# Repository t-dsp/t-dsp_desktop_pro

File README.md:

# T-DSP Desktop Pro

**Part of the [T-DSP](https://t-dsp.com) open modular audio platform.**

A desktop audio backplane (120mm x 100mm) that serves as the central hub for the T-DSP modular audio ecosystem. Hosts a Teensy 4.1, ESP32, and T-DSP TAC5212 pro audio codec module on an 8-layer PCB designed for studio-quality signal integrity.

| | |
|:---:|:---:|
|  |  |
|  |  |

**[View 3D Render Gallery](https://t-dsp.github.io/t-dsp_desktop_pro/gallery.html)** -- interactive slideshow of all board views

## About T-DSP

T-DSP is an open modular audio platform designed for musicians, engineers, and developers who want powerful digital signal processing in a flexible, hackable format. Built around the [Teensy](https://www.pjrc.com/teensy/) microcontroller and the [Teensy Audio Library](https://www.pjrc.com/teensy/td_libs_Audio.html), T-DSP combines studio-quality audio with a growing library of open-source modules for mixing, synthesis, effects, and more.

Whether you're building a custom digital mixer, crafting a unique instrument, or prototyping audio products, T-DSP gives you the tools to bring your ideas to life.

Join the community, contribute to the library, or grab a module and start patching. Learn more at [t-dsp.com](https://t-dsp.com).

## Overview

The Desktop Pro is a **backplane PCB** that hosts a Teensy 4.1, ESP32, and T-DSP codec module alongside supporting ICs to create a complete audio development platform. It provides all the connectors, processing, networking, and user interface needed to build desktop audio devices.

## Processing

- **Teensy 4.1** -- ARM Cortex-M7 running the Teensy Audio Library for real-time audio processing (mixing, effects, synthesis, routing). Also receives USB Audio.
- **ESP32** -- UI controller, WiFi/Bluetooth connectivity. Runs the display, buttons, and encoder, and sends commands to the Teensy over serial.
- **T-DSP TAC5212 Module** -- Professional stereo audio codec (ADC + DAC) with mic preamp, line, and instrument inputs

## On-Board ICs

| Ref | Part | Function |
|-----|------|----------|
| U1 | Teensy 4.1 | Audio DSP (ARM Cortex-M7) |
| U2 | ESP32-DevKitC | UI controller, WiFi/Bluetooth |
| U3 | TPS2116DRL | Power multiplexer (dual input selection) |
| U4 | H11L1SM | Optoisolator (MIDI input) |
| U5-U8 | SN74LVC2G125DCTR | Dual bus buffers (4x) |
| U9 | 74HCT2G17GW | Dual Schmitt trigger buffer |
| U10 | TPD4E02B04DQA | USB ESD protection (4-channel) |
| IC1 | 74HCT2G125DC | Logic level shifter |
| D5 | TPD1E10B06DPYT | VBUS ESD protection |
| Q1, Q2 | DMG2307L-7 | P-FET reverse polarity protection |

## Connectivity

### Audio I/O
- **RCA outputs** -- Stereo analog audio output
- **RCA inputs** -- Stereo analog audio input
- **Headphone output** -- 1/4" (6.35mm) or 3.5mm headphone jack
- **S/PDIF** -- Digital audio input and output

### USB
- **USB-C DEVICE** -- Power and USB Audio to Teensy with ESD protection (TPD4E02B04 + TPD1E10B06)
- **USB-A HOST** -- USB host connector

### MIDI
- **MIDI input** -- 3.5mm TRS with optical isolation (H11L1)
- **MIDI GPIO** -- Configurable for MIDI in, out, or thru

### Power
- **Dual power input** -- USB-C or external supply via JST-XH header, with TPS2116 power multiplexer for automatic switchover
- **Reverse polarity protection** -- P-channel MOSFET (DMG2307L-7) on both 5V and 12V inputs
- **Power indicators** -- LED indicators for 5V and 12V rails

### Storage
- **SD card** -- Accessible via Teensy 4.1 built-in SD slot

## Expansion

- **2x TDM expansion headers** (2x10 pin, 2.54mm) -- Connect T-DSP audio modules
  - TDM digital audio bus (BCLK, LRCK, DATA_IN, DATA_OUT, MCLK)
  - I2C control bus (SDA, SCL)
  - Power rails (3.3V, 5V, 12V, GND)
  - Control pins (Held-high, Held-low)
- Modules can be soldered directly or socketed with pin headers
- Multiple modules can be chained on the same TDM bus

## User Interface

The backplane exposes interface-ready GPIO headers for flexible UI connectivity, supporting popular interface options compatible with the ESP32.

- **GPIO header** -- Active-low buttons, rotary encoder, and display connections for tactile UI
- **OLED display header** (128x64, SSD1306) -- Status and menu-driven UI
- **3.2" TFT touchscreen header** (ILI9341) -- Touchscreen UI
- **SK6812 addressable LED header** -- ESP32 and Teensy status indication, plus LED strip control

## Board Design

- **8-layer PCB** with dedicated ground and power planes for low-noise analog performance
- **120mm x 100mm** board dimensions
- LDO voltage regulation for clean analog power
- Buffered digital outputs for reliable module distribution
- Separate analog and digital ground domains

## Project Files

| Directory | Contents |
|-----------|----------|
| `/3d_models/` | 3D models for PCB components |
| `/documentation/` | [Schematic PDF](documentation/t-dsp-desktop-pro-schematic.pdf), board images, and reference docs |
| `/lib_fp/` | Custom KiCad footprint libraries |
| `/lib_sch/` | Custom KiCad schematic symbol libraries |
| `/manufacturing/` | CI-generated manufacturing outputs (gerbers, BOM, pick & place, PDFs) |
| `/panel/` | Panelized board layouts for production |
| `/pages/` | [3D Render Gallery](https://t-dsp.github.io/t-dsp_desktop_pro/gallery.html), [Interactive BOM](https://t-dsp.github.io/t-dsp_desktop_pro/ibom.html) |

View the design files directly in your browser with KiCanvas: [Schematic](https://kicanvas.org/?github=https://github.com/t-dsp/t-dsp_desktop_pro/blob/main/t-dsp_desktop_pro.kicad_sch) | [PCB](https://kicanvas.org/?github=https://github.com/t-dsp/t-dsp_desktop_pro/blob/main/t-dsp_desktop_pro.kicad_pcb)

## Status

This board is under active development. The current revision includes USB-C ESD protection, reverse polarity protection, and boot pin corrections from the pre-production review.

If you build one, we'd love to hear how it goes -- please open an issue or reach out with your findings.

## Contact

For consulting, custom backplane design, or commercial licensing inquiries, reach out via [LinkedIn](https://linkedin.com/in/jayshoe).

## License

This project is licensed under the [Creative Commons Attribution-NonCommercial-ShareAlike 4.0 International (CC BY-NC-SA 4.0)](https://creativecommons.org/licenses/by-nc-sa/4.0/).

You are free to share and adapt this work for non-commercial purposes, as long as you give appropriate credit and distribute any derivatives under the same license.

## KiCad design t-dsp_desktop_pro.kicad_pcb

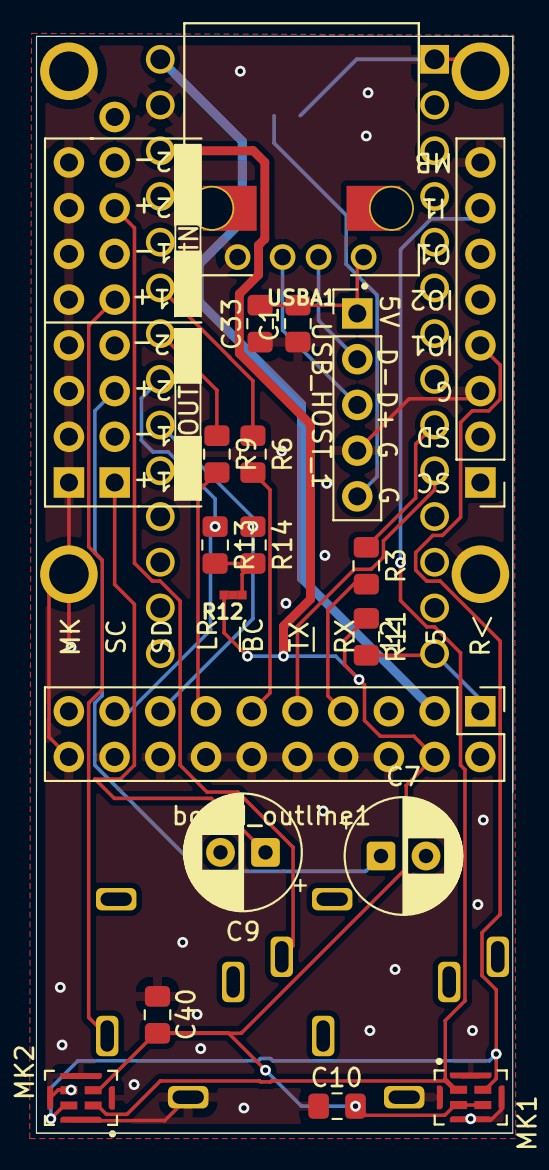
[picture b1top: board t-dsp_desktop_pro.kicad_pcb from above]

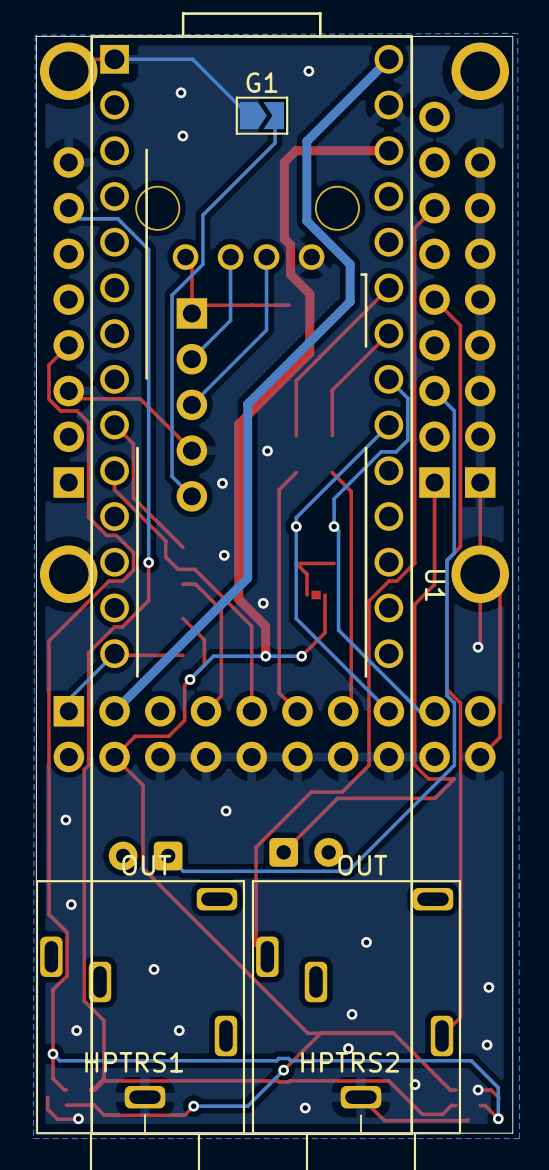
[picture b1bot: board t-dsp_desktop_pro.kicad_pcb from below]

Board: 2 copper layers, 26.5 x 60.9 mm, 22 parts (4 on the bottom side), 24 nets.

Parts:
C1: 1 uF; C_0805_2012Metric_Pad1.15x1.40mm_HandSolder
C7, C9: 470 uF Electrolytic Audio-Grade; CP_Radial_D6.3mm_P2.50mm
C10, C40: 0.1uF; C_0805_2012Metric_Pad1.15x1.40mm_HandSolder
C33: 10 uF; C_0805_2012Metric_Pad1.15x1.40mm_HandSolder
G1: jumper; SolderJumper-2_P1.3mm_Open_TrianglePad1.0x1.5mm
HPTRS1, HPTRS2: 3.5mm TRS - 35RAPC3BH3; 35RAPC3BH3
MK1, MK2: SPK0641HT4H-1
R3, R6, R9: 49.9 ohm; R_0805_2012Metric_Pad1.15x1.40mm_HandSolder
R11: 10k; R_0805_2012Metric_Pad1.15x1.40mm_HandSolder
R12: 0 ohm; jumper_slice
R13, R14: 2.21k ohm; R_0805_2012Metric_Pad1.15x1.40mm_HandSolder
U1: Teensy 4.1 - DEVKIT; Teensy41_simple
USBA1: USB A Host - TE 292303-5; TE_292303-5_USB_A_tight_fit
USB_HOST_1: header; USB_IN1
board_outline1: TAC5212 Module; audio_module_board_outline_50x34.5_d1_ADAPTOR

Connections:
3.3V: C10.1, C40.1, MK1.3 (SELECT), MK1.4 (VDD), MK2.4 (VDD), R11.1, R12.2, U1.46 (3V3), board_outline1.4 (3.3V)
5V: U1.48 (VIN), board_outline1.3 (5V)
7_OUT1A: R3.2, board_outline1.7 (DSP_DOUT)
8_IN1: U1.10 (8_TX2_IN1), board_outline1.9 (DSP_DIN)
35_TX8_RESET: R11.2, U1.14 (12_MISO_MQSL), board_outline1.1 (HELD_HIGH)
/AUDIO_IN1P: HPTRS2.5, board_outline1.29 (IN1P)
/AUDIO_IN2P: HPTRS2.2, board_outline1.33 (IN2P)
/AUDIO_OUT2P: C7.1, board_outline1.25 (OUT2P)
/AUDIO_OUTP: C9.1, board_outline1.21 (OUTP)
BCLK1: R6.2, board_outline1.11 (BCLK)
GND: C1.2, C10.2, C33.2, C40.2, G1.1, HPTRS1.1, HPTRS2.1, MK1.5 (GND), MK1.6 (GND), MK1.7 (GND), MK1.8 (GND), MK2.3 (SELECT), MK2.5 (GND), MK2.6 (GND), MK2.7 (GND), MK2.8 (GND), U1.1 (GND), U1.47 (GND), USBA1.4 (GND), USB_HOST_1.4 (GND), board_outline1.6 (GNDD), board_outline1.8 (GNDD), board_outline1.10 (GNDD), board_outline1.12 (GNDD), board_outline1.14 (GNDD), board_outline1.16 (GNDD), board_outline1.18 (GNDD), board_outline1.20 (GNDD), board_outline1.22 (AGND), board_outline1.24 (AGND), board_outline1.26 (AGND), board_outline1.28 (AGND), board_outline1.30 (AGND), board_outline1.32 (AGND), board_outline1.34 (AGND), board_outline1.36 (AGND), board_outline1.39 (GNDD), board_outline1.44 (GNDD), board_outline1.49 (AGND), board_outline1.50 (AGND), board_outline1.51 (DGND), board_outline1.52 (DGND)
GPIGPI1: MK1.1 (DATA), MK2.1 (DATA), board_outline1.43 (GPI1)
GPIO1: MK1.2 (CLOCK), MK2.2 (CLOCK), board_outline1.40 (GPIO1)
HOST_5V: C1.1, C33.1, USBA1.1 (VBUS), USB_HOST_1.1 (5V)
HOST_D1+: USBA1.3 (D+), USB_HOST_1.3 (D1+)
HOST_D1-: USBA1.2 (D-), USB_HOST_1.2 (D1-)
LRCK1: R9.2, board_outline1.13 (LRCK)
unnamed: R12.1, R13.2, R14.2
unnamed: R3.1, U1.9 (7_RX2_OUT1A)
unnamed: R9.1, U1.42 (20_A6_TX5_LRCLK1)
unnamed: R6.1, U1.43 (21_A7_RX5_BCLK1)
SCL0: R13.1, U1.41 (19_A5_SCL), board_outline1.17 (SCL)
SDA0: R14.1, U1.40 (18_A4_SDA), board_outline1.15 (SDA)
USB_SHIELD2: G1.2, USB_HOST_1.5 (SHIELD)

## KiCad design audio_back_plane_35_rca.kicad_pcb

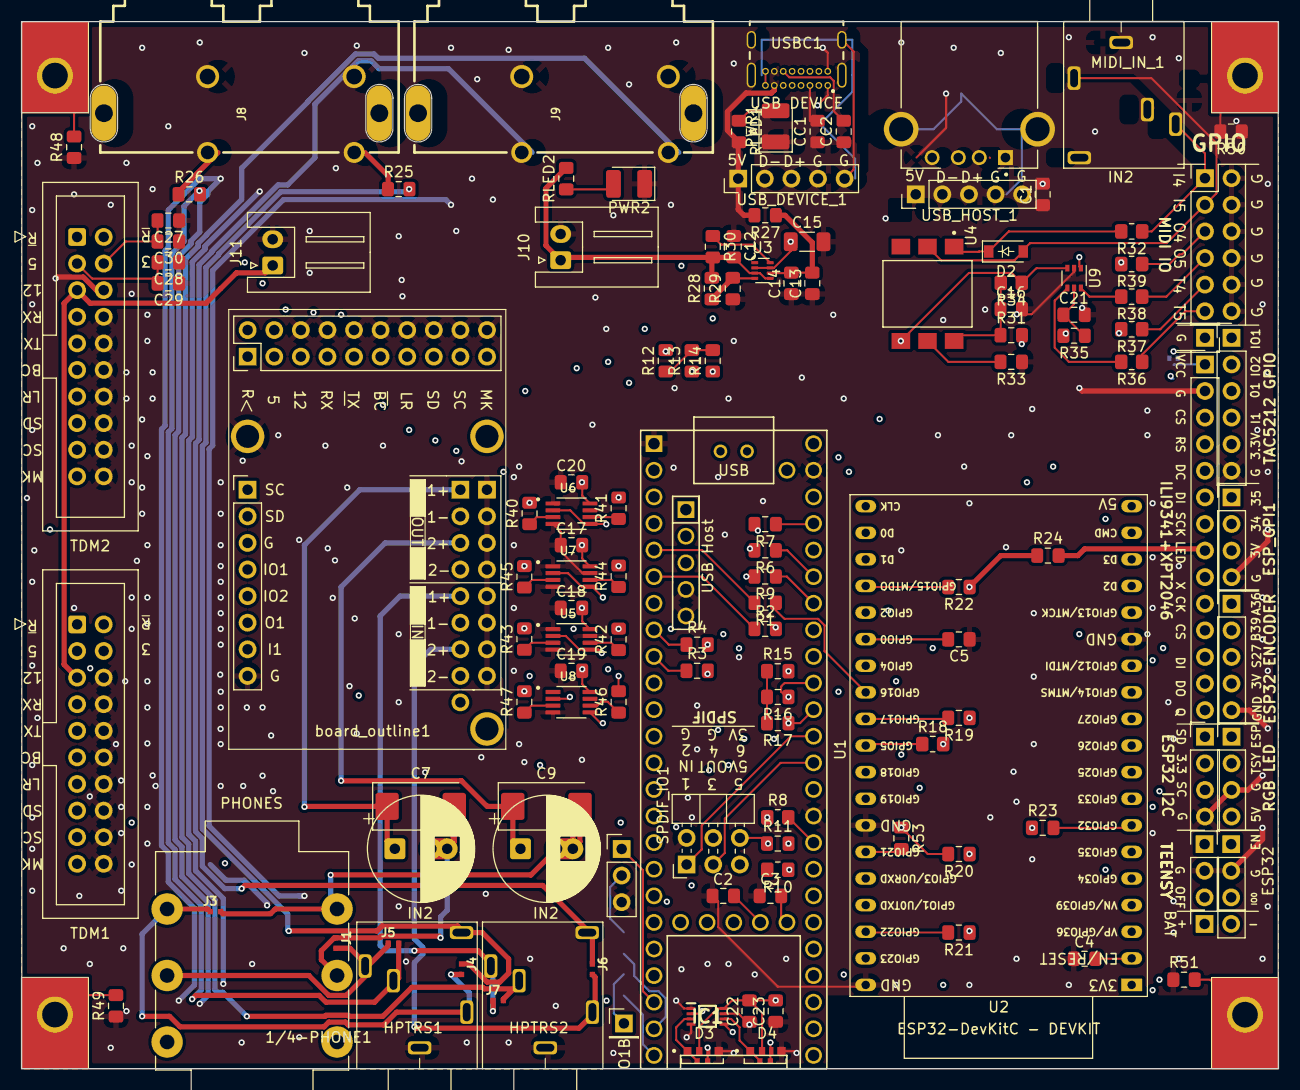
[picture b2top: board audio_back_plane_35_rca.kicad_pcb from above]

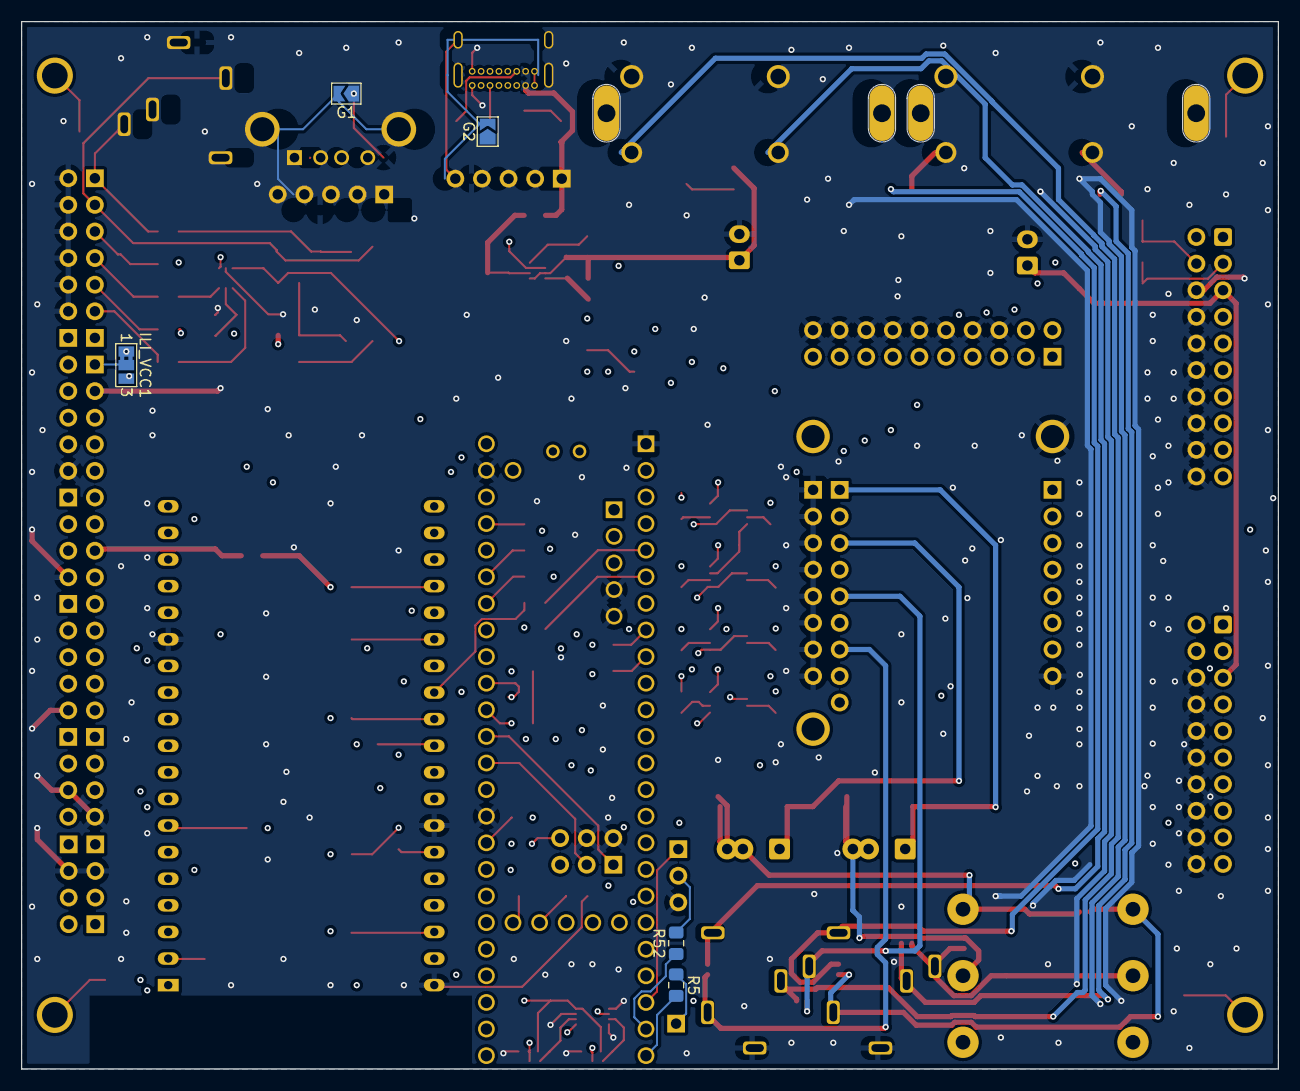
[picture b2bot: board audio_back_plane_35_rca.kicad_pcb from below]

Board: 8 copper layers, 120.0 x 100.0 mm, 138 parts (5 on the bottom side), 143 nets.

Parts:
1/4-PHONE1: NMJ6HFD2-AU; Jack_6.35mm_Neutrik_NMJ6HCD3_Horizontal
BAT1: BAT HEADER; BAT2_PinSocket_1x02_P2.54mm_Vertical
C1, C29, C30: 1 uF; C_0805_2012Metric_Pad1.15x1.40mm_HandSolder
C2, C3, C4, C5, C14, C16, C17, C18, C19, C20, C21, C22: 0.1 uF; C_0805_2012Metric_Pad1.15x1.40mm_HandSolder
C7, C9: 470 uF Electrolytic Audio-Grade; CP_Radial_D10.0mm_P5.00mm_AND_D8.0mm_P3.5mm
C12, C13, C23: 10 uF; C_0805_2012Metric_Pad1.15x1.40mm_HandSolder
C15: 100 uF; C_1206_3216Metric_Pad1.33x1.80mm_HandSolder
C27, C28: 47uF; C_0805_2012Metric_Pad1.15x1.40mm_HandSolder
CC1, CC2: 5.1k ohm; R_0805_2012Metric_Pad1.15x1.40mm_HandSolder
D1: HEADER; TAC5212 GPIO_PinHeader_1x06_P2.54mm_Vertical
D2: Diode - 1N4148; D_SOD-123
D3, D4: Side Light LED - SK6812; SK6812-32228SMD-Reverse-Mount_mod
ESP_I1: ESP32 I2C HEADER; ESP_I2C_PinHeader_1x04_P2.54mm_Vertical
ESP_PROG1: header; E_PROG1_PinHeader_1x03_P2.54mm_Vertical
ESP_R_ENC1: header; ESP_R_ENC0_PinHeader_1x05_P2.54mm_Vertical
G1, G2: jumper; SolderJumper-2_P1.3mm_Open_TrianglePad1.0x1.5mm
GPI1: ESP32 GPI HEADER; GPI1_PinHeader_1x04_P2.54mm_Vertical
HPTRS1, HPTRS2: 3.5mm TRS - 35RAPC3BH3; 35RAPC3BH3
IC1: Logic Level Shifter - 74HCT2G125DC,125; SOP50P310X100-8N
ILI1: ILI9341+XPT2046; ILI9341_PinHeader_1x14_P2.54mm_Vertical
ILI_VCC1: jumper; SolderJumper-3_P1.3mm_Bridged2Bar12_Pad1.0x1.5mm_NumberLabe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
J1, J3, J4, J5, J6, J7: jumper; jumper_slice_disconnected
J2: GROUND HEADER; GPIO_GROUND_PinHeader_1x01_P2.54mm_Vertical
J8, J9: PJRAS2X1S01X; PJRAS2X1S01X_MOD2
J10, J11: JST-XH Connector -; JST_XH_S2B-XH-A_1x02_P2.50mm_Horizontal
J12: RGB LED HEADEER; LED_GPIO_PinHeader_1x04_P2.54mm_Vertical
J14: Conn_01x03; Teensy_UART3_PinHeader_1x03_P2.54mm_Vertical
J15: Conn_01x01; OUT1B_PinHeader_1x01_P2.54mm_Vertical
MIDI_IN_1: 3.5mm TRS - 35RAPC3BH3; 35RAPC3BH3
MIDI_IO1: header; MIDI_IO1
PWR1, PWR2: LED Power Indicator - 1206 5v 2.0 V Forward; D_1210_3225Metric_Pad1.42x2.65mm_HandSolder
R1, R2, R3, R4, R5, R6, R7, R9, R25, R26, R40, R41, R42, R43, R44, R45, R46, R47, R52, R53: 49.9 ohm; R_0805_2012Metric_Pad1.15x1.40mm_HandSolder
R8, R18, R32, R34, R36, R37, R38, R39: 220 ohm; R_0805_2012Metric_Pad1.20x1.40mm_HandSolder
R10: 49.9 ohm; R_0805_2012Metric_Pad1.20x1.40mm_HandSolder
R11, R13, R14, R16, R17, R19, R20, R21, R22, R23: 2.21k ohm; R_0805_2012Metric_Pad1.15x1.40mm_HandSolder
R12, R15, R24, R27, R31, R35, R48, R49, R50, R51: 0 ohm; R_0805_2012Metric_Pad1.15x1.40mm_HandSolder
R28: 16.9k ohm; R_0805_2012Metric_Pad1.15x1.40mm_HandSolder
R29, R30: 5.1k ohm; R_0805_2012Metric_Pad1.15x1.40mm_HandSolder
R33: 1.5k ohm; R_0805_2012Metric_Pad1.15x1.40mm_HandSolder
RLED1, RLED2: 2.21k ohm; R_0805_2012Metric_Pad1.15x1.40mm_HandSolder
SPDIF_IO1: header; SPDIF_PinHeader_2x03_P2.54mm_Horizontal
T108, T109, T110, T111: Tab
TDM1, TDM2: I2S /I2C EXPANSION HEADER; T-DSP_Expansion_Header_2x10_ALT_GND
T_PROG1: TEENSY SWITCH HEADER; T_PROG1_PinHeader_1x03_P2.54mm_Vertical
U1: Teensy 4.1 - DEVKIT; Teensy41_mod3
U2: ESP32-DevKitC - DEVKIT; ESP32-DevKitC_NO_COURTYARD
U3: Power Mux & Protect - TPS2116DRL; SOT-583-8
U4: Optoisolators - H11L1SM - 6-SMD, Gull Wing; IC_H11L1SM
U5, U6, U7, U8: Dual Buffer - SN74LVC2G125DCTR; SOP65P400X130-8N
U9: Dual Buffer - 74HCT2G17GW,125; SOT-363_SC-70-6
USBA1: USB A Host - TE 292303-5; TE_292303-5_USB_A
USBC1: USB C Port - Through Hole USB4085-GF-A; GCT_USB4085-GF-A_REVA4
USB_DEVICE_1: header; USB_IN1
USB_HOST_1: header; USB_IN1
board_outline1: TAC5212 Module; audio_module_board_outline_50x34.5_d1_mod
board_outline2: board_outline; audio_project_board_outline_100x120

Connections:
2_OUT2: U1.4 (2_OUT2), U2.8 (32K_XN/GPIO33/ADC1_CH5)
3.3V: C17.1, C18.1, C19.1, C20.1, C27.1, C30.1, D1.5, ESP_I1.2, ESP_R_ENC1.4, GPI1.3, ILI_VCC1.3 (B), R11.1, R12.2, R15.2, R19.1, R20.1, R21.1, R22.1, R23.1, R24.1, R31.2, SPDIF_IO1.6, TDM1.4 (GND), TDM2.4 (GND), U1.46 (3V3), U5.8 (VCC), U6.8 (VCC), U7.8 (VCC), U8.8 (VCC), board_outline1.4 (GNDD)
3_LRCLK2: R1.1, U2.27 (GPIO16)
4_BCLK2: R2.2, U2.10 (DAC_2/ADC2_CH9/GPIO26)
5V: C15.1, C22.1, C23.1, C28.1, C29.1, D3.2 (VDD), D4.2 (VDD), IC1.8 (VCC), ILI_VCC1.1 (A), J12.4, R35.2, R37.2, R39.2, SPDIF_IO1.5, TDM1.3 (5V), TDM2.3 (5V), U1.48 (VIN), U2.19 (5V), U3.2 (VOUT), U3.7 (VOUT), board_outline1.3 (5V)
5V_JST: C12.1, J10.1, R28.2, R30.2, RLED2.2, U3.3 (VIN1), U3.5 (MODE)
5V_USB: R27.2, RLED1.2, USBC1.A4 (VBUS), USBC1.A9 (VBUS), USBC1.B4 (VBUS), USBC1.B9 (VBUS), USB_DEVICE_1.1 (5V)
5_IN2: U1.7 (5_IN2), U2.9 (DAC_1/ADC2_CH8/GPIO25)
6_OUT1D: R4.2, U8.5 (2A)
6_OUT1D+: R47.2, TDM1.9 (DSP_DATA_OUT)
7_OUT1A: R3.2, U8.2 (1A)
7_OUT1A+: R46.2, TDM2.9 (DSP_DATA_OUT), board_outline1.7 (DSP_DOUT)
8_IN1: TDM2.7 (DSP_DATA_IN), U1.10 (8_TX2_IN1), board_outline1.9 (DSP_DIN)
9_OUT1C_INPUT: TDM1.7 (DSP_DATA_IN), U1.11 (9_OUT1C)
12V: J11.1, TDM1.5 (12V), TDM2.5 (12V)
14_SPDIF_OUT: SPDIF_IO1.3, U1.36 (14_A0_TX3_SPDIF_OUT)
15_SPDIF_IN: SPDIF_IO1.1, U1.37 (15_A1_RX3_SPDIF_IN)
32_OUT1B: J15.1, R5.1
34_RX8_RESET2: TDM1.2 (HELD_LOW), TDM2.2 (HELD_LOW), U1.26 (34_RX8), board_outline1.2 (HELD_LOW)
35_TX8_RESET: R11.2, TDM1.1 (HELD_HIGH), TDM2.1 (HELD_HIGH), U1.27 (35_TX8), board_outline1.1 (HELD_HIGH)
53_T_PROG: C2.1, T_PROG1.1, U1.53 (PROGRAM)
54_ON_OFF: C3.1, T_PROG1.3, U1.54 (ON_OFF)
/AUDIO_IN1P: HPTRS2.2, J7.2, board_outline1.29 (IN1P)
/AUDIO_IN2P: HPTRS2.5, J6.1, board_outline1.33 (IN2P)
/AUDIO_OUT2P: C9.1, board_outline1.25 (OUT2P)
/AUDIO_OUTP: C7.1, board_outline1.21 (OUTP)
/ESP32_IO1: U1.20 (28_RX7), U2.35 (U0TXD/GPIO1)
/ESP32_IO3: U1.21 (29_TX7), U2.34 (U0RXD/GPIO3)
/ESP32_IO21_SDA: R53.2, U2.33 (GPIO21)
/ESP32_IO22_SCL: ESP_I1.3, R21.2, U2.36 (GPIO22)
/OUTPUTA: ESP_R_ENC1.1, U1.32 (40_A16), U2.3 (SENSOR_VP/GPIO36/ADC1_CH0)
/OUTPUTB: ESP_R_ENC1.2, U1.31 (39_MISO1_OUT1A), U2.4 (SENSOR_VN/GPIO39/ADC1_CH3)
/SWITCH: ESP_R_ENC1.3, U1.30 (38_CS1_IN1), U2.11 (ADC2_CH7/GPIO27)
BCLK1: R6.2, U7.2 (1A), U7.5 (2A)
BCLK1+TDM1: R44.2, TDM2.11 (BCLK), board_outline1.11 (BCLK)
BCLK1+TDM2: R45.2, TDM1.11 (BCLK)
DEVICE_D1+: U1.67 (D+), USBC1.A6 (DP1), USB_DEVICE_1.3 (D1+)
DEVICE_D1-: U1.66 (D-), USBC1.A7 (DN1), USB_DEVICE_1.2 (D1-)
ESP32_EN: C4.1, ESP_PROG1.1, U1.29 (37_CS), U2.2 (EN/CHIP_PU/RESET)
ESP32_IO0: C5.1, ESP_PROG1.3, U1.28 (36_CS), U2.25 (*GPIO0/BOOT/ADC2_CH1)
ESP32_IO12_SPI_MISO: U1.14 (12_MISO_MQSL), U2.13 (*MTDI/GPIO12/ADC2_CH5)
ESP32_IO13_SPI_MOSI: U1.13 (11_MOSI_CTX1), U2.15 (MTCK/GPIO13/ADC2_CH4)
ESP32_IO14_SPI_SCK: U1.35 (13_SCK_LED), U2.12 (MTMS/GPIO14/ADC2_CH6)
ESP32_IO33_SPI_CS: R19.2, U1.12 (10_CS_MQSR), U2.28 (GPIO17)
ESP32_LED: IC1.2 (1A), R18.2
ESP32_LED+: D4.1 (DIN), IC1.6 (1Y)
ESP32_LED_OUT: D4.3 (DOUT), J12.1
GND: C1.2, C2.2, C3.2, C4.2, C5.2, C12.2, C13.2, C14.2, C15.2, C16.1, C17.2, C18.2, C19.2, C20.2, C21.1, C22.2, C23.2, C27.2, C28.2, C29.2, C30.2, CC1.1, CC2.1, D1.6, D3.4 (GND), D4.4 (GND), ESP_I1.4, ESP_PROG1.2, ESP_R_ENC1.5, G1.1, G2.1, GPI1.4, HPTRS1.1, HPTRS2.1, IC1.1 (~1OE), IC1.4 (GND), IC1.7 (~2OE), ILI1.2 (GND), J8.S1, J8.S2, J9.S1, J9.S2, J10.2, J11.2, J12.3, J14.3, MIDI_IN_1.1, MIDI_IO1.2, MIDI_IO1.4, MIDI_IO1.6, MIDI_IO1.8, MIDI_IO1.10, MIDI_IO1.12, PWR1.1 (K), PWR2.1 (K), R29.1, R33.1, R48.1, R49.1, R50.1, R51.1, SPDIF_IO1.2, SPDIF_IO1.4, TDM1.6 (GND), TDM1.8 (GND), TDM1.10 (GND), TDM1.12 (GND), TDM1.14 (GND), TDM1.16 (GND), TDM1.18 (GND), TDM1.20 (GND), TDM2.6 (GND), TDM2.8 (GND), TDM2.10 (GND), TDM2.12 (GND), TDM2.14 (GND), TDM2.16 (GND), TDM2.18 (GND), TDM2.20 (GND), T_PROG1.2, U1.1 (GND), U1.34 (GND), U1.47 (GND), U1.58 (GND), U1.59 (GND), U2.14 (GND), U2.32 (GND), U2.38 (GND), U5.1 (~1OE), U5.4 (GND), U5.7 (~2OE), U6.1 (~1OE), U6.4 (GND), U6.7 (~2OE), U7.1 (~1OE), U7.4 (GND), U7.7 (~2OE), U8.4 (GND), U9.2 (GND), USBA1.4 (GND), USBC1.A1 (GND), USBC1.A12 (GND), USBC1.B1 (GND), USBC1.B12 (GND), USB_DEVICE_1.4 (GND), USB_HOST_1.4 (GND), board_outline1.6 (GNDD), board_outline1.8 (GNDD), board_outline1.10 (GNDD), board_outline1.12 (GNDD), board_outline1.14 (GNDD), board_outline1.16 (GNDD), board_outline1.18 (GNDD), board_outline1.20 (GNDD), board_outline1.22 (AGND), board_outline1.24 (AGND), board_outline1.26 (AGND), board_outline1.28 (AGND), board_outline1.30 (AGND), board_outline1.32 (AGND), board_outline1.34 (AGND), board_outline1.36 (AGND), board_outline1.44 (GNDD), board_outline1.51 (DGND)
HOST_5V: C1.1, U1.55 (5V), USBA1.1 (VBUS), USB_HOST_1.1 (5V)
HOST_D1+: U1.57 (D+), USBA1.3 (D+), USB_HOST_1.3 (D1+)
HOST_D1-: U1.56 (D-), USBA1.2 (D-), USB_HOST_1.2 (D1-)
LRCK1: R9.2, U5.2 (1A), U5.5 (2A)
LRCK1+TDM1: R42.2, TDM2.13 (LRCK), board_outline1.13 (LRCK)
LRCK1+TDM2: R43.2, TDM1.13 (LRCK)
MCLK1: R7.2, U6.2 (1A), U6.5 (2A)
MCLK1+TDM1: R41.2, TDM2.19 (MCLK), board_outline1.19 (MCLK)
MCLK1+TDM2: R40.2, TDM1.19 (MCLK)
MIDI_IN_4: MIDI_IN_1.2, MIDI_IO1.1, R32.1
MIDI_IN_5: D2.2 (A), MIDI_IN_1.5, MIDI_IO1.3, U4.2
MIDI_OUT_4: MIDI_IO1.5, R39.1
MIDI_OUT_5: MIDI_IO1.7, R38.1
MIDI_RX: R34.1, U1.2 (0_RX1_CRX2_CS1), U4.4, U9.3
MIDI_THRU_4: MIDI_IO1.9, R37.1
MIDI_THRU_5: MIDI_IO1.11, R36.1
MIDI_TX_T: U1.3 (1_TX1_CTX2_MISO1), U9.1
unnamed: 1/4-PHONE1.R, C7.2, J1.2
unnamed: 1/4-PHONE1.RN, HPTRS1.2, J1.1, J5.2
unnamed: 1/4-PHONE1.T, C9.2, J3.1
unnamed: 1/4-PHONE1.TN, HPTRS1.5, J3.2, J4.1
unnamed: BAT1.1, U1.50 (VBAT)
unnamed: BAT1.2, U1.52 (GND)
unnamed: C16.2, R31.1, R34.2, U4.6
unnamed: D1.1, board_outline1.40 (GPIO1)
unnamed: D1.2, board_outline1.41 (GPIO2)
unnamed: D1.3, board_outline1.42 (GPO1)
unnamed: D1.4, board_outline1.43 (GPI1)
unnamed: D2.1 (K), R32.2, U4.1
unnamed: ESP_I1.1, R20.2, R53.1
unnamed: GPI1.1, U2.6 (VDET_2/GPIO35/ADC1_CH7)
unnamed: GPI1.2, U2.5 (VDET_1/GPIO34/ADC1_CH6)
unnamed: HPTRS1.3, J5.1, R26.2
unnamed: HPTRS1.4, J4.2, R25.2
unnamed: HPTRS2.3, J7.1, J9.T1
unnamed: HPTRS2.4, J6.2, J9.T2
unnamed: ILI1.3 (CS), R22.2, U2.23 (*MTDO/GPIO15/ADC2_CH3)
unnamed: ILI1.5 (DC), U2.24 (ADC2_CH2/*GPIO2)
unnamed: ILI1.8 (LED_(3.3V)), R24.2
unnamed: ILI1.4 (RESET), U2.26 (ADC2_CH0/GPIO4)
unnamed: ILI1.7 (SCK), ILI1.10 (T_CLK(SCK)), U2.30 (GPIO18)
unnamed: ILI1.6 (SDI(MOSI)), ILI1.12 (T_DIN(MOSI)), U2.37 (GPIO23)
unnamed: ILI1.9 (SDO(MISO)), ILI1.13 (T_DO(MISO)), U2.31 (GPIO19)
unnamed: ILI1.11 (T_CS), R23.2, U2.7 (32K_XP/GPIO32/ADC1_CH4)
unnamed: ILI1.1 (VCC_(5V)), ILI_VCC1.2 (C)
unnamed: J8.T1, R25.1
unnamed: J8.T2, R26.1
unnamed: J14.1, U1.22 (30_CRX3)
unnamed: J14.2, R52.2
unnamed: PWR1.2 (A), RLED1.1
unnamed: PWR2.2 (A), RLED2.1
unnamed: R12.1, R13.2, R14.2
unnamed: R15.1, R16.2, R17.2
unnamed: R33.2, U4.5
unnamed: R36.2, U9.4
unnamed: R38.2, U9.6
unnamed: R48.2, board_outline2.1 (GND)
unnamed: R49.2, board_outline2.2 (GND)
unnamed: R50.2, board_outline2.3 (GND)
unnamed: R51.2, board_outline2.4 (GND)
unnamed: R1.2, U1.5 (3_LRCLK2)
unnamed: R2.1, U1.6 (4_BCLK2)
unnamed: R4.1, U1.8 (6_OUT1D)
unnamed: R3.1, U1.9 (7_RX2_OUT1A)
unnamed: R9.1, U1.42 (20_A6_TX5_LRCLK1)
unnamed: R6.1, U1.43 (21_A7_RX5_BCLK1)
unnamed: R7.1, U1.45 (23_A9_CRX1_MCLK1)
unnamed: R52.1, U1.23 (31_CTX3)
unnamed: R5.2, U1.24 (32_OUT1B)
unnamed: R10.1, U1.25 (33_MCLK2)
unnamed: R8.2, U1.33 (41_A17)
unnamed: R18.1, U2.29 (*GPIO5)
unnamed: R28.1, R29.2, U3.4 (PR1)
unnamed: R30.1, U3.8 (ST)
unnamed: R42.1, U5.6 (1Y)
unnamed: R43.1, U5.3 (2Y)
unnamed: R41.1, U6.6 (1Y)
unnamed: R40.1, U6.3 (2Y)
unnamed: R44.1, U7.6 (1Y)
unnamed: R45.1, U7.3 (2Y)
unnamed: R46.1, U8.6 (1Y)
unnamed: R47.1, U8.3 (2Y)
unnamed: C21.2, R35.1, U9.5 (VCC)
unnamed: CC1.2, USBC1.A5 (CC1)
unnamed: CC2.2, USBC1.B5 (CC2)
SCL0: R13.1, TDM2.17 (SCL), U1.41 (19_A5_SCL), board_outline1.17 (SCL)
SCL1: R17.1, TDM1.17 (SCL), U1.38 (16_A2_RX4_SCL1)
SDA0: R14.1, TDM2.15 (SDA), U1.40 (18_A4_SDA), board_outline1.15 (SDA)
SDA1: R16.1, TDM1.15 (SDA), U1.39 (17_A3_TX4_SDA1)
TEENSY_LED: IC1.5 (2A), R8.1
TEENSY_LED+: D3.1 (DIN), IC1.3 (2Y)
TEENSY_LED_OUT: D3.3 (DOUT), J12.2
USB_SHIELD: G2.2, USBC1.S1 (SHELL), USBC1.S2 (SHELL), USBC1.S3 (SHELL), USBC1.S4 (SHELL), USB_DEVICE_1.5 (SHIELD)
USB_SHIELD2: G1.2, USBA1.5 (Shield), USB_HOST_1.5 (SHIELD)
VIN2_SECONDARY: C13.1, C14.1, R27.1, U3.6 (VIN2)

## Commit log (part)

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2025-04-06 added tft touchscreen
2025-04-08 added touchscreen
2026-02-07 Rename project to t-dsp_desktop_pro, add LICENSE and README
    Rename all project files, internal references, gerbers, and BOM from
    audio_back_plane_35_rca to t-dsp_desktop_pro. Add CC BY-NC-SA 4.0
    license and README modeled after the TAC5212 module repo. Update
    .gitignore to match t-dsp standards.
2026-02-07 Clean up repo for public release
    Move snapshot archives, SolidWorks bundles, duplicate 3D models, and
    old enclosure assembly files to 3d_models/_unused/. Move third-party
    datasheets from lib_docs/ to documentation/_reference/. Remove lib_dl/
    (raw component library downloads) from tracking. All directories are
    gitignored to keep them local. Matches the t-dsp_tac5212 repo structure.
2026-02-07 Add board images, schematic PDF, and update README
    Add 3D renders (top, bottom, front angle, back angle), PCB layout
    screenshot, and schematic PDF to documentation/. Update README with
    inline images and corrected project files table.
2026-02-07 Show all 4 board images together at top of README
2026-02-07 Clarify USB-C/USB-B are shared footprint options
2026-02-07 Update README: add on-board ICs table, refine processing and board design sections
    Add IC reference table (Teensy, ESP32, TPS2116, H11L1, bus buffers,
    Schmitt triggers). Update Processing to clarify ESP32 runs UI and
    Teensy handles audio/USB Audio. Remove TVS/ferrite references from
    Board Design (those are on the TAC5212 module, not the backplane).
2026-02-07 Update overview to describe Desktop Pro as a complete audio development platform
2026-02-07 Rewrite connectivity and UI sections with accurate hardware details
    Fix audio I/O: RCA in/out, dual headphone jack options, MIDI input
    with GPIO for in/out/thru. Add dual power, SD card, and USB power/audio.
    Update UI section: GPIO header for flexible connectivity, LEDs for
    both ESP32 and Teensy.
2026-02-08 Add 3D STL export and KiCanvas viewer links to README
2026-02-11 Add KiBot CI pipeline, bundle 3D models locally, fix Blender renders
    - Add .kibot.yaml with full manufacturing outputs (gerbers, BOM, 3D renders)
    - Add GitHub Actions workflow for automated manufacturing file generation
    - Bundle ~26 standard KiCad library 3D models into 3d_models/ so they
    resolve in Docker/CI without a KiCad installation
    - Rewrite all PCB model paths from ${KISYS3DMOD}/${KICAD*_3DMODEL_DIR}
    to ${KIPRJMOD}/3d_models/ for portable resolution
2026-02-11 Clean up local artifacts and update .gitignore
    Add ignore rules for .claude/, ibom.config.ini, *.kicad_pro-bak, and
    nul. Remove .claude/settings.local.json from tracking.
2026-02-11 Add 3D render gallery to GitHub Pages
    Create a self-contained HTML slideshow (pages/gallery.html) showing all
    16 Blender renders with All Components / SMD Only tabs, keyboard nav,
    and thumbnail strip. Deploy renders alongside the iBOM to GitHub Pages.
2026-02-19 created expansion board outline with headers
2026-02-19 modularize
2026-02-20 Localize all 3D model paths for Docker/CI rendering
    Rewrite all 3D model references from system variables (KICAD9_3DMODEL_DIR,
    KISYS3DMOD, KICAD6/8_3DMODEL_DIR) to ${KIPRJMOD}/3d_models/ so models
    resolve correctly in Docker-based KiBot CI builds. Copy 45 standard KiCad
    3D models to the project. Fix BOM field mismatches for RLED1/RLED2 and
    R36/R39 grouping. Update schematic symbol library and footprint libraries.
2026-02-23 v0.8: Pre-production review - USB ESD, reverse polarity, boot pin fixes
    - Add USB-C ESD protection: TPD4E02B04 (D+/D-/CC1/CC2) + TPD1E10B06 (VBUS)
    - Add P-FET reverse polarity protection: DMG2307L-7 on 5V and 12V inputs
    - Fix USB-C reversibility: tie DP1+DP2 and DN1+DN2 together
    - Add ESP32 GPIO12 pull-down (10k) for 3.3V flash boot
    - Add ESP32 GPIO17 CS pull-up (10k)
    - Change SPI CS pull-ups R19/R22/R23 from 2.21k to 10k
2026-02-23 v0.81: Fix CI release, localize 3D models, update README with render gallery
    - Fix workflow: add gh release create before upload (tag != release)
    - Fix ZIP filename: remove empty %r board revision from output name
    - Localize 3D model paths for U10, C15, JST connectors to ${KIPRJMOD}
    - Add project-local footprints for C_1206 and JST_XH_S2B-XH-A
    - Trim SMD 3D renders from 8 to 4 views (top, bottom, top_iso, bottom_iso)
    - Update gallery.html to handle different view counts per set
2026-02-24 v0.82: Fix audio output pin mapping and add PTC fuse footprint
    - Correct L/R channel assignment: Left=OUT1, Right=OUT2
    - Fix tip/ring polarity: +=tip, -=ring
    - Add PTC resettable fuse (MF-LSMF300) footprint and 3D model
    - Update workflow to include tag in manufacturing ZIP filename
2026-02-24 v0.8.4: Production release - final layout and schematic updates
